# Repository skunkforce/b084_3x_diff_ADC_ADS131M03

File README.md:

# edgy_board number b084
This design is part of the [edgy board project](https://github.com/skunkforce/edgy_boards). 

# getting started
This repository uses submodules. After cloning use the command 

```$ git submodule update --init --recursive```

to pull the submodules before opening the project with kicad. 

# Tests
Tests can be found in [TESTS.md](TESTS.md)

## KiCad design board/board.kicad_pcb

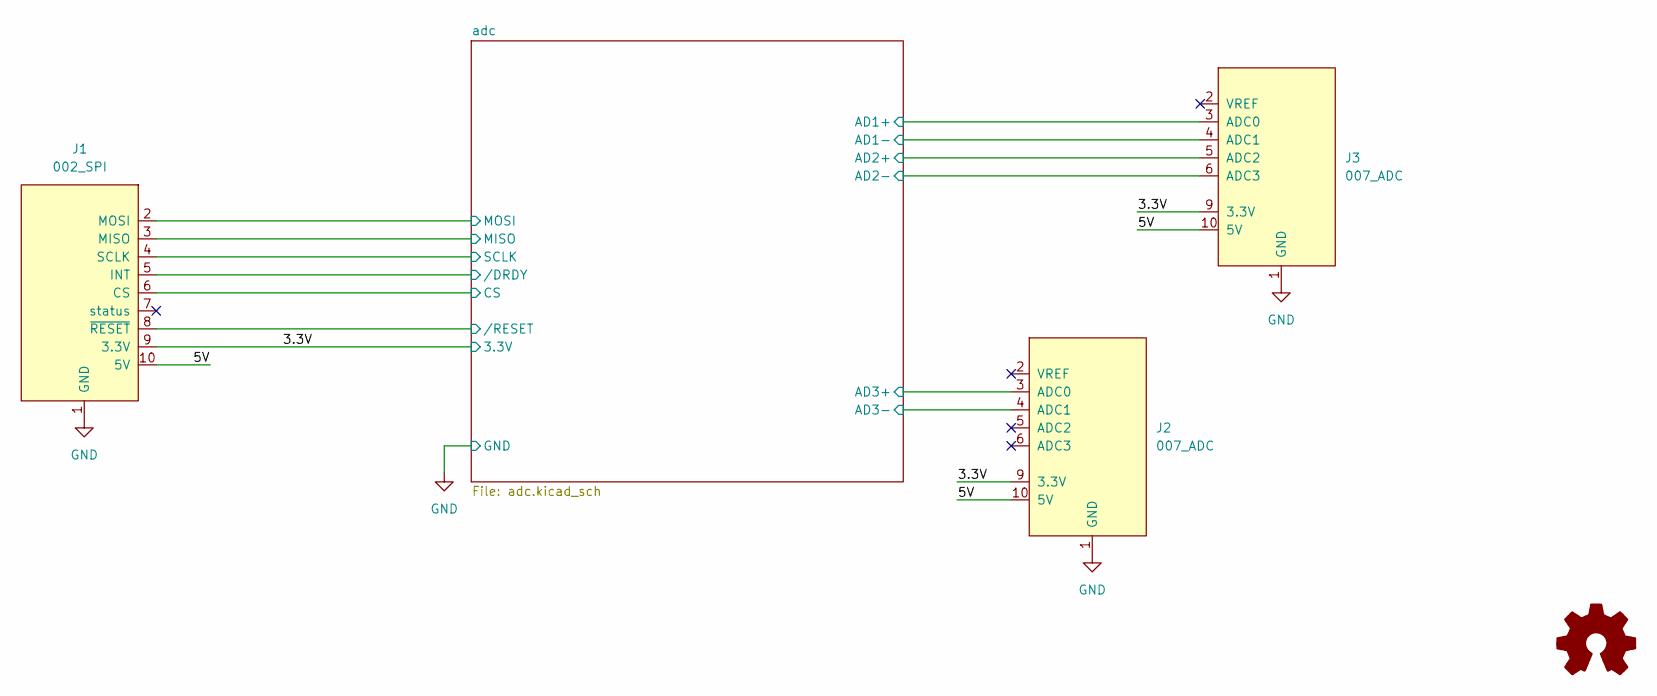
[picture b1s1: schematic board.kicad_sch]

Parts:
J1: 002_SPI; on_edge_2x05_device
J2, J3: 007_ADC; on_edge_2x05_host
LOGO1: Logo_Open_Hardware_Small; OSHW-Symbol_6.7x6mm_SilkScreen

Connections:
/3.3V: J1.9 (3.3V), J2.9 (3.3V), J3.9 (3.3V); also elsewhere on the board
/5V: J1.10 (5V), J2.10 (5V), J3.10 (5V)
/adc/AD1+: J3.3 (ADC0); also elsewhere on the board
/adc/AD1-: J3.4 (ADC1); also elsewhere on the board
/adc/AD2+: J3.5 (ADC2); also elsewhere on the board
/adc/AD2-: J3.6 (ADC3); also elsewhere on the board
/adc/AD3+: J2.3 (ADC0); also elsewhere on the board
/adc/AD3-: J2.4 (ADC1); also elsewhere on the board
/adc/CS: J1.6 (CS); also elsewhere on the board
/adc/MISO: J1.3 (MISO); also elsewhere on the board
/adc/MOSI: J1.2 (MOSI); also elsewhere on the board
/adc/SCLK: J1.4 (SCLK); also elsewhere on the board
/adc//DRDY: J1.5 (INT); also elsewhere on the board
/adc//RESET: J1.8 (~RESET); also elsewhere on the board
GND: J1.1 (GND), J2.1 (GND), J3.1 (GND); also elsewhere on the board

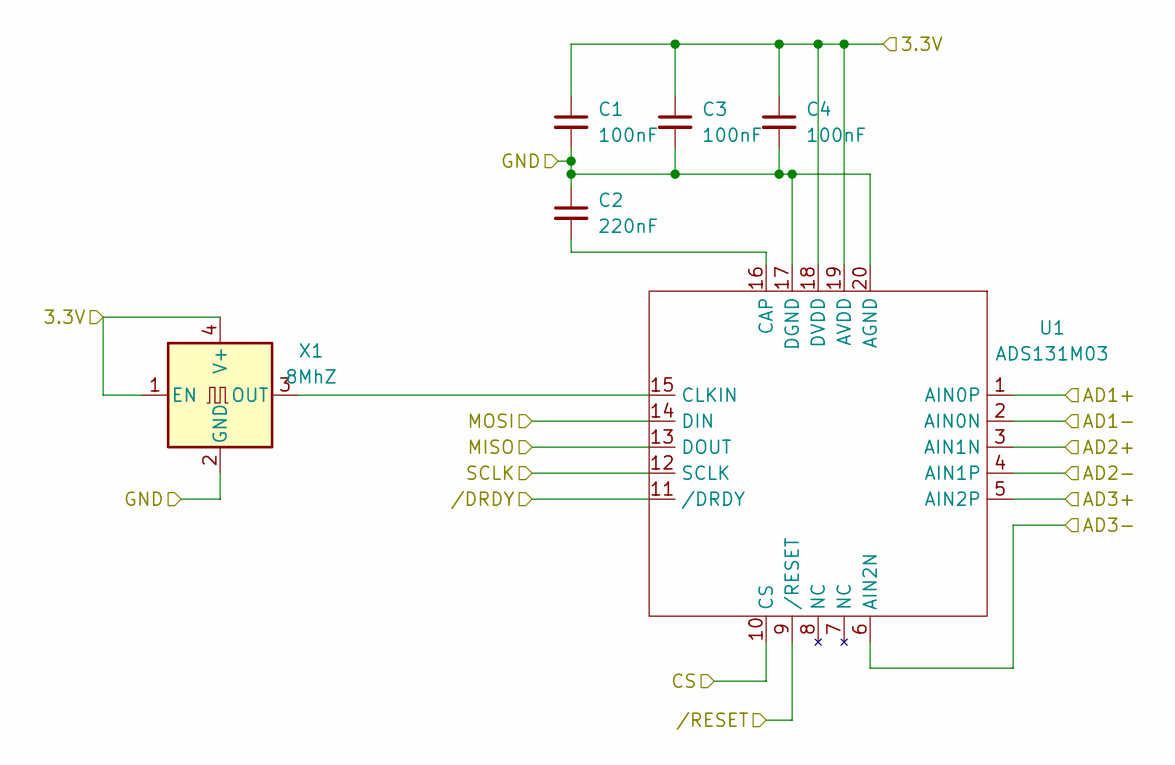
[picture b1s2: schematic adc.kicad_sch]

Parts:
C1, C3, C4: 100nF; C_0603_1608Metric
C2: 220nF; C_0603_1608Metric
U1: ADS131M03; WQFN-20-1EP_3x3mm_P0.4mm_EP1.7x1.7mm
X1: 8MhZ; Oscillator_SMD_EuroQuartz_XO32-4Pin_3.2x2.5mm; MPN O 8,0-JO32-B-1V3-1-T1-LF

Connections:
/3.3V: C1.1, C3.1, C4.1, U1.18 (DVDD), U1.19 (AVDD), X1.1 (EN), X1.4 (V+); also elsewhere on the board
/adc/AD1+: U1.1 (AIN0P); also elsewhere on the board
/adc/AD1-: U1.2 (AIN0N); also elsewhere on the board
/adc/AD2+: U1.3 (AIN1N); also elsewhere on the board
/adc/AD2-: U1.4 (AIN1P); also elsewhere on the board
/adc/AD3+: U1.5 (AIN2P); also elsewhere on the board
/adc/AD3-: U1.6 (AIN2N); also elsewhere on the board
/adc/CS: U1.10 (CS); also elsewhere on the board
/adc/MISO: U1.13 (DOUT); also elsewhere on the board
/adc/MOSI: U1.14 (DIN); also elsewhere on the board
/adc/SCLK: U1.12 (SCLK); also elsewhere on the board
/adc//DRDY: U1.11 (/DRDY); also elsewhere on the board
/adc//RESET: U1.9 (/RESET); also elsewhere on the board
GND: C1.2, C2.1, C3.2, C4.2, U1.17 (DGND), U1.20 (AGND), X1.2 (GND); also elsewhere on the board
unnamed: C2.2, U1.16 (CAP)
unnamed: U1.15 (CLKIN), X1.3 (OUT)

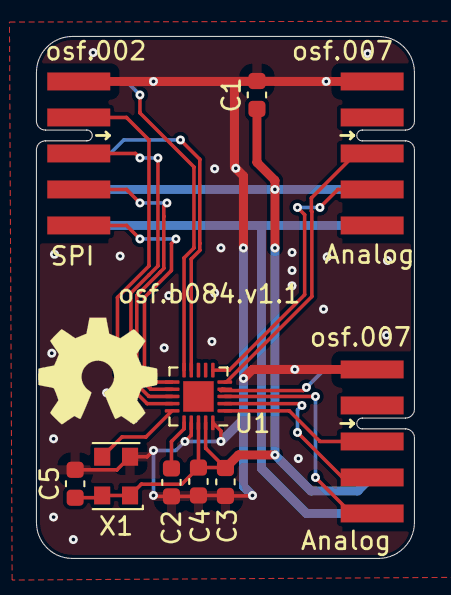
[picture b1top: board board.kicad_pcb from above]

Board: 2 copper layers, 21.0 x 29.0 mm, 11 parts (0 on the bottom side), 17 nets.

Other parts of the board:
C5: 100nF; C_0603_1608Metric

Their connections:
/3.3V: C5.1; also elsewhere on the board
GND: C5.2; also elsewhere on the board

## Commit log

2023-02-17 initial
2023-02-27 fixed silkscreen
2023-03-29 added ground pours, a picture and decoupling for the oscillator
